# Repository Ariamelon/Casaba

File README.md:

# Casaba
USB-C breakout board with integrated protection.

## Disclaimer
This board is a USB daughterboard to be used in custom mechanical keyboard projects, allowing the implementation of most electrical protection required in a keyboard via a tested, proven PCB. It also allows the replacement of the USB-C port in case it is damaged during use. The shape of the board and the positions of the M3 mounting holes and USB-C connector is based on the [Unified Daughterboard](https://unified-daughterboard.github.io/) [UDB-S](https://unified-daughterboard.github.io/#/db-spec-s), allowing for easy swap-in functionality.

## Key Features
* "Wide and narrow" 40mm wide x 9mm deep x 1.6mm thick form factor.
    - Avoids obstacles such as weights commonly found in custom keyboards.
    - Mountable both right-side-up and upside-down.
* 2 x M3 mounting points.
* Cheap to source via JLC assembly.
* Large DB corner radii which allow keyboard cases to be milled at a large inner radius.
* ESD protection, overcurrent protection, overvoltage protection, noise filtering, and single-point ground to chassis functionality.
* Breaks out CC pins in addition to USB pins.
* On-board solder jumpers allowing the user to connect 5k1 pull-downs to the CC pins if breaking them out is not required.

## Changelog
* 06/04/2023: Initial commit

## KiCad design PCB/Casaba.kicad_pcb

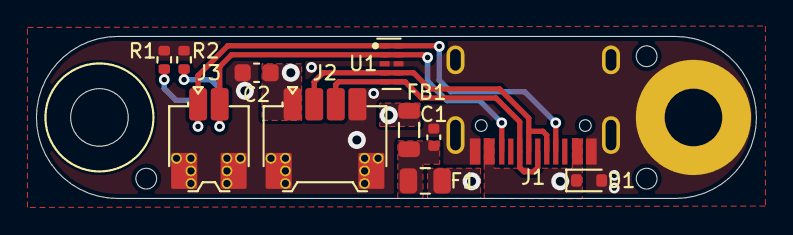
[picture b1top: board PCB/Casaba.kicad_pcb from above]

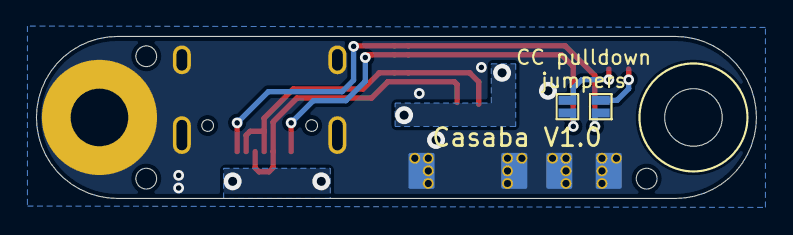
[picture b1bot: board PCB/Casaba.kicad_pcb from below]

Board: 2 copper layers, 40.0 x 9.0 mm, 19 parts (4 on the bottom side), 10 nets.

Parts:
A1: Ariamelon Logo; Ariamelon_Logo-CU
C1: 10n; C_0402_1005Metric
C2: 1u; C_0603_1608Metric
D1: 5V; D_SOD-523
F1: 5V 3A; Fuse_0805_2012Metric
FB1: 60R@100MHz; L_0805_2012Metric
H1: Earth; MountingHole_3.2mm_M3_Pad
H2: M3; MountingHole_3.2mm_M3
H3, H4, H5: JLC Tooling; JLC Tooling Hole
J1: USB_C_Receptacle_USB2.0; HRO-TYPE-C-31-M-12
J2: 78171-0004; Molex_Pico-EZmate_78171-0004_1x04-1MP_P1.20mm_Vertical
J3: 78171-0002; Molex_Pico-EZmate_78171-0002_1x02-1MP_P1.20mm_Vertical
JP1: CC1_5K1; SolderJumper-2_P1.3mm_Open_Pad0.5x1.0mm
JP2: CC2_5K1; SolderJumper-2_P1.3mm_Open_Pad0.5x1.0mm
R1, R2: 5k1; R_0402_1005Metric
U1: TPD4E05U06DQAR; USON-10_2.5x1.0mm_P0.5mm

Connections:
+5V: C2.1, FB1.1, J2.1
/CC1: J1.A5 (CC1), J3.1, JP1.1 (A), U1.1 (IO1), U1.10 (NC)
/CC2: J1.B5 (CC2), J3.2, JP2.1 (A), U1.2 (IO2), U1.9 (NC)
/D+: J1.A6 (D+), J1.B6 (D+), J2.3, U1.5 (IO4), U1.6 (NC)
/D-: J1.A7 (D-), J1.B7 (D-), J2.2, U1.4 (IO3), U1.7 (NC)
GND: C1.1, C2.2, D1.2 (A), H1.1, J1.A1 (GND), J1.A12 (GND), J1.S1 (SHIELD), J2.4, J2.MP (MountPin), J3.MP (MountPin), R1.2, R2.2, U1.3 (GND), U1.8 (GND)
unnamed: C1.2, F1.2, FB1.2
unnamed: JP1.2 (B), R1.1
unnamed: JP2.2 (B), R2.1
VBUS: D1.1 (K), F1.1, J1.A4 (VBUS), J1.A9 (VBUS)

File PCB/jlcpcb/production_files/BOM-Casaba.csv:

Comment,Designator,Footprint,LCSC
TPD4E05U06DQAR,U1,USON-10_2.5x1.0mm_P0.5mm,C138714
10n,C1,C_0402_1005Metric,C15195
1u,C2,C_0603_1608Metric,C15849
USB_C_Receptacle_USB2.0,J1,HRO-TYPE-C-31-M-12,C165948
5V 3A,F1,Fuse_0805_2012Metric,C207025
60R@100MHz,FB1,L_0805_2012Metric,C237300
5k1,"R1,R2",R_0402_1005Metric,C25905
5V,D1,D_SOD-523,C502546
78171-0002,J3,Molex_Pico-EZmate_78171-0002_1x02-1MP_P1.20mm_Vertical,C505023
78171-0004,J2,Molex_Pico-EZmate_78171-0004_1x04-1MP_P1.20mm_Vertical,C588524

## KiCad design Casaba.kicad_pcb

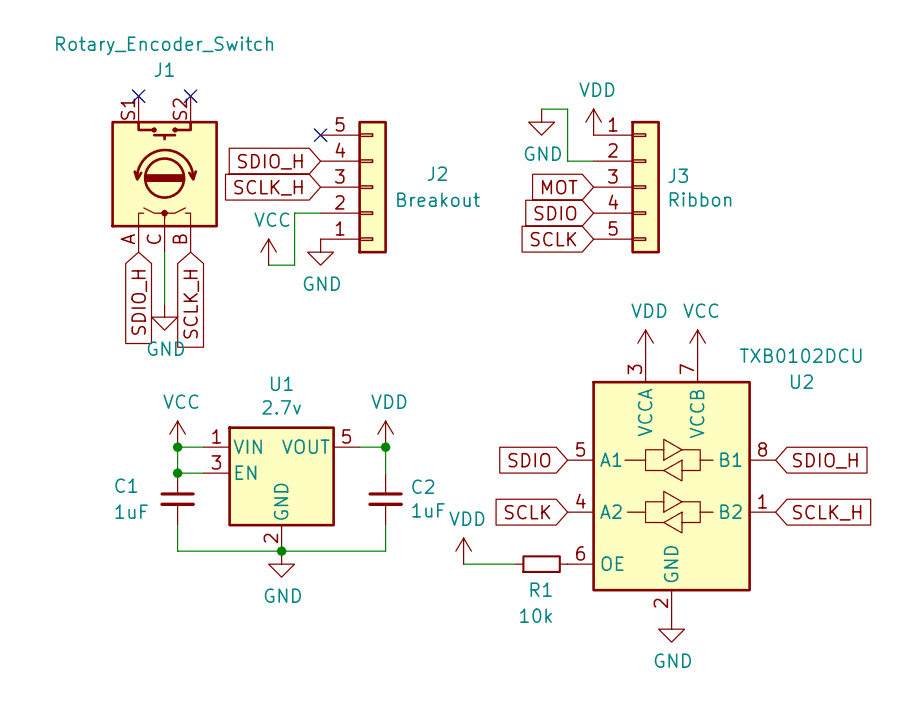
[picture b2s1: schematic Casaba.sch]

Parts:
C1, C2: 1uF; C_0603_1608Metric
J1: Rotary_Encoder_Switch; RotaryEncoder_Alps_EC11E-Switch_Vertical_H20mm
J2: Breakout; PinHeader_1x05_P2.54mm_Vertical
J3: Ribbon; PinHeader_1x05_P1.27mm_Vertical
R1: 10k; R_0603_1608Metric
U1: 2.7v; SOT-23-5
U2: TXB0102DCU; VSSOP-8_2.4x2.1mm_P0.5mm

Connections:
GND: C1.2, C2.2, J1.C, J2.1, J3.2, U1.2 (GND), U2.2 (GND)
MOT: J3.3
unnamed: R1.2, U2.6 (OE)
SCLK: J3.5, U2.4 (A2)
SCLK_H: J1.B, J2.3, U2.1 (B2)
SDIO: J3.4, U2.5 (A1)
SDIO_H: J1.A, J2.4, U2.8 (B1)
VCC: C1.1, J2.2, U1.1 (VIN), U1.3 (EN), U2.7 (VCCB)
VDD: C2.1, J3.1, R1.1, U1.5 (VOUT), U2.3 (VCCA)

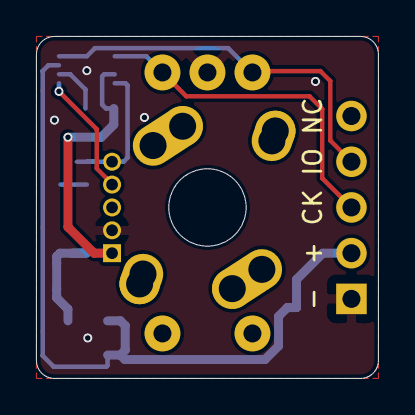
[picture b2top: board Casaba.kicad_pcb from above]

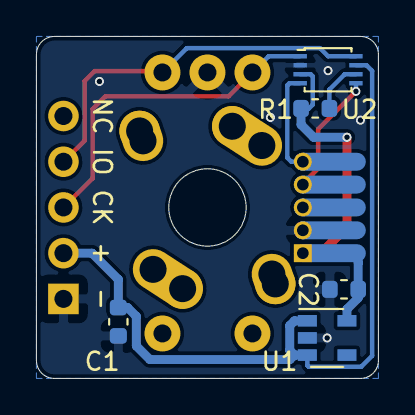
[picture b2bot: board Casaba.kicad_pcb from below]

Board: 2 copper layers, 19.0 x 19.0 mm, 8 parts (6 on the bottom side), 8 nets.

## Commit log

2020-10-26 Added license
2023-04-06 Initial commit.
